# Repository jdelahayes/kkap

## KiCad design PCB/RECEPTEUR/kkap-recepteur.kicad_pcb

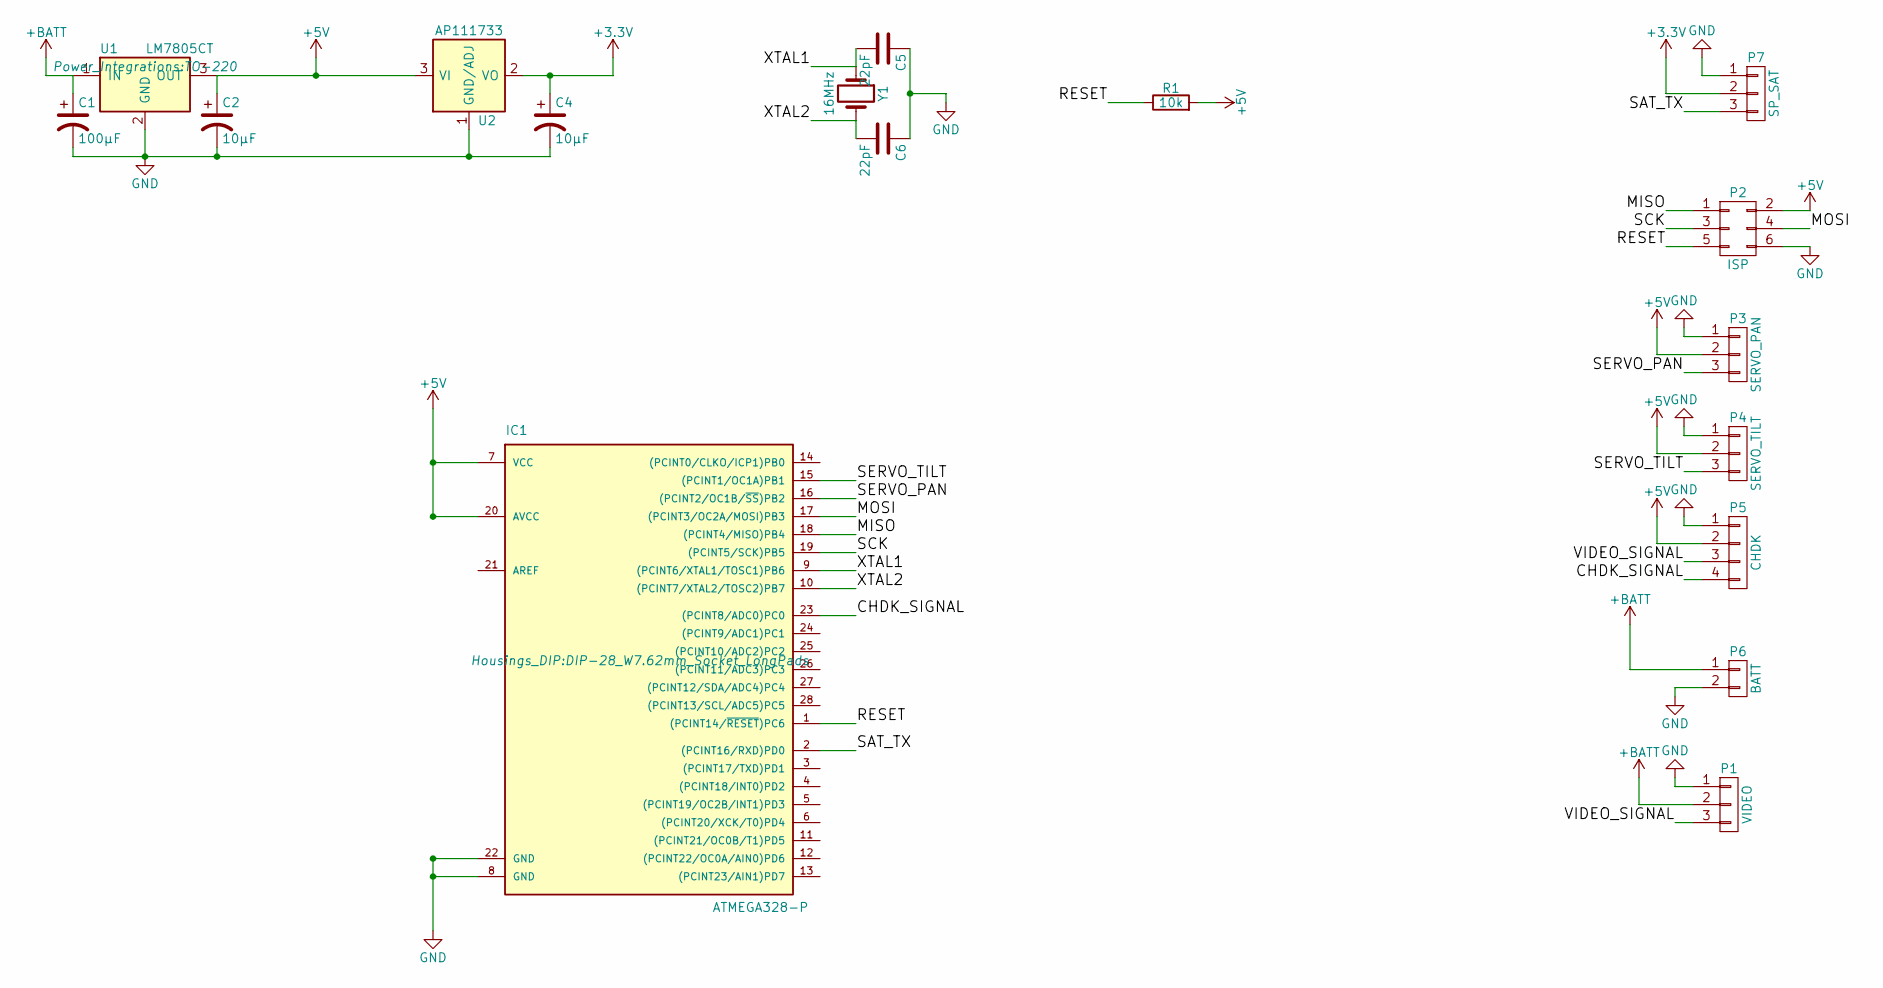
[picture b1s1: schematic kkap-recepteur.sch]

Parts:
C1: 100µF; C_Radial_D5_L6_P2.5
C2, C4: 10µF; C_Radial_D5_L6_P2.5
C5, C6: 22pF; C_Disc_D3_P2.5
IC1: ATMEGA328-P; DIP-28_W7.62mm_Socket_LongPads
P1: VIDEO; Pin_Header_Straight_1x03_Pitch2.54mm
P2: ISP; Pin_Header_Straight_2x03_Pitch2.54mm
P3: SERVO_PAN; Pin_Header_Straight_1x03_Pitch2.54mm
P4: SERVO_TILT; Pin_Header_Straight_1x03_Pitch2.54mm
P5: CHDK; Pin_Header_Straight_1x04_Pitch2.54mm
P6: BATT; Pin_Header_Straight_1x02_Pitch2.54mm
P7: SP_SAT; Pin_Header_Straight_1x03_Pitch2.54mm
R1: 10k; Resistor_Horizontal_RM7mm
U1: LM7805CT; TO-220
U2: AP111733; SOT-223
Y1: 16MHz; Crystal_HC49-U_Vertical

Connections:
+3V3: C4.1, P7.2, U2.2 (VO), U2.4 (VO)
+5V: C2.1, IC1.7 (VCC), IC1.20 (AVCC), P2.2, P3.2, P4.2, P5.2, R1.2, U1.3 (OUT), U2.3 (VI)
+BATT: C1.1, P1.2, P6.1, U1.1 (IN)
/CHDK_SIGNAL: IC1.23 ((PCINT8/ADC0)PC0), P5.4
/MISO: IC1.18 ((PCINT4/MISO)PB4), P2.1
/MOSI: IC1.17 ((PCINT3/OC2A/MOSI)PB3), P2.4
/RESET: IC1.1 ((PCINT14/~RESET~)PC6), P2.5, R1.1
/SAT_TX: IC1.2 ((PCINT16/RXD)PD0), P7.3
/SCK: IC1.19 ((PCINT5/SCK)PB5), P2.3
/SERVO_PAN: IC1.16 ((PCINT2/OC1B/~SS~)PB2), P3.3
/SERVO_TILT: IC1.15 ((PCINT1/OC1A)PB1), P4.3
/VIDEO_SIGNAL: P1.3, P5.3
/XTAL1: C5.2, IC1.9 ((PCINT6/XTAL1/TOSC1)PB6), Y1.1
/XTAL2: C6.2, IC1.10 ((PCINT7/XTAL2/TOSC2)PB7), Y1.2
GND: C1.2, C2.2, C4.2, C5.1, C6.1, IC1.8 (GND), IC1.22 (GND), P1.1, P2.6, P3.1, P4.1, P5.1, P6.2, P7.1, U1.2 (GND), U2.1 (GND/ADJ)

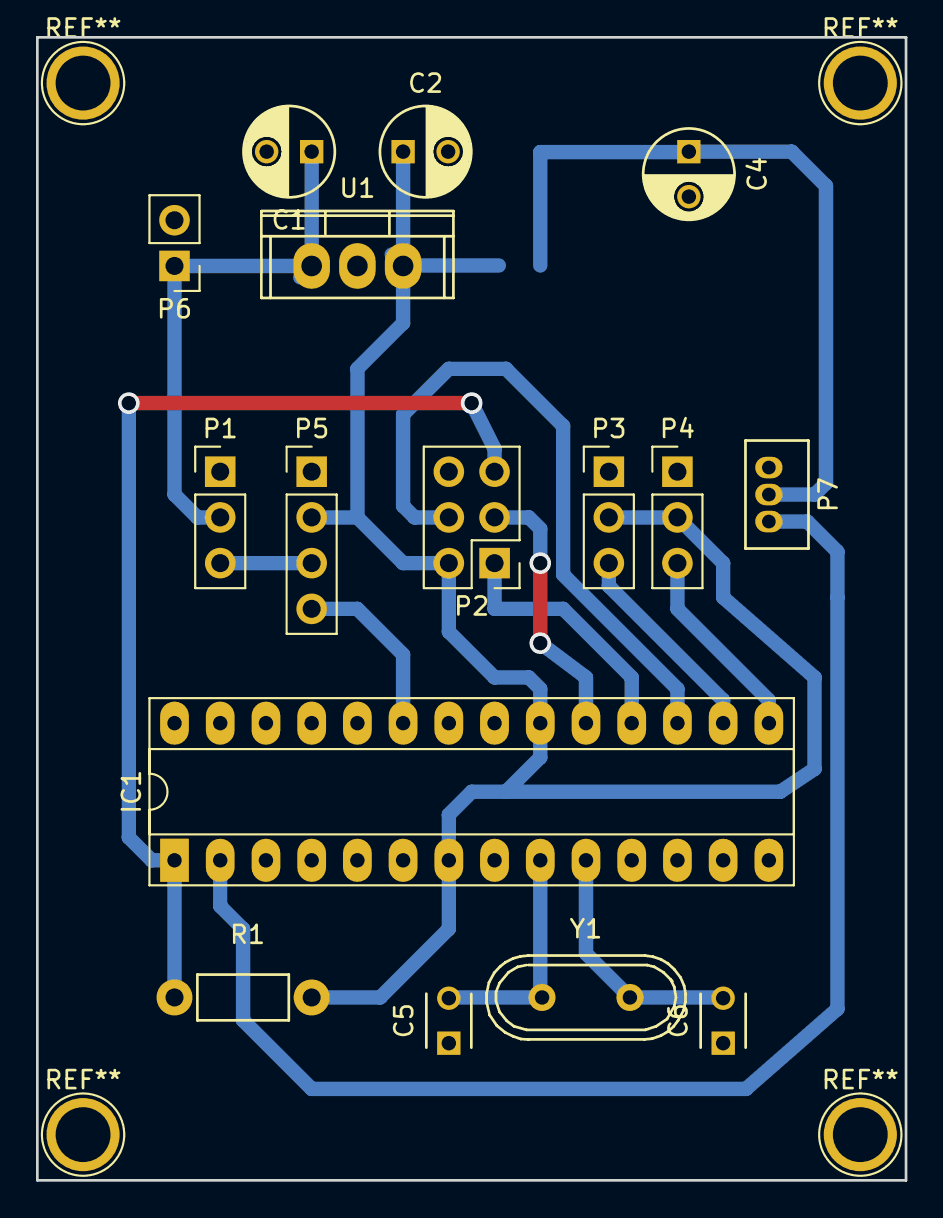
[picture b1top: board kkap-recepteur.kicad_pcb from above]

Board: 2 copper layers, 48.3 x 63.5 mm, 17 parts (1 on the bottom side), 15 nets.

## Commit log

2017-01-01 Initialisation
2017-01-01 Ajout datasheet
2017-01-02 PCB V1
2017-01-03 Modification du sat
    Modification du pin header par un connecteur JST-ZH pour le satellite spektrum
